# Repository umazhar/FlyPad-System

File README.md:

# FlyPadUI and STROBE

## Overview
FlyPadUI (Sip TRiggered Optogenetic Behavior Enclosure) is a Python-based user interface for tracking fly sips, calculating preference indices, and providing a convenient graphical interface for data analysis. The software connects to the STROBE device to record and analyze feeding behavior in flies.

The original STROBE UI was built in Visual Studio 2012 in C++ on Windows 10 and required installation of Qt 5.11 to compile. The current Python-based version maintains compatibility with the STROBE device while providing improved usability and analysis capabilities.

## Requirements
- Python (latest version)
- Dependencies listed in `requirements.txt`

## Installation

1. Clone this repository:
```bash
git clone https://github.com/umazhar/STROBE.git
cd /SOFTWARE/STROBE_UI
```

2. Create and activate a virtual environment

**For Linux/Mac (Terminal):**
```bash
python -m venv venv
source venv/bin/activate
```

**For Windows (Command Prompt):**
```cmd
python -m venv venv
venv\Scripts\activate.bat
```

**For Windows (PowerShell):**
```powershell
python -m venv venv
.\venv\Scripts\Activate.ps1
```

1. Install required dependencies:
```bash
pip install -r requirements.txt
```

## Usage

Run the main application:
```bash
python main.py
```

All output data will be stored in the `output` folder.

## File Structure
```
/SOFTWARE/STROBE_UI/
├── main.py           # Main application entry point
├── requirements.txt  # Dependencies
├── venv/             # Virtual environment (generated on setup)
└── output/           # Output data directory
```

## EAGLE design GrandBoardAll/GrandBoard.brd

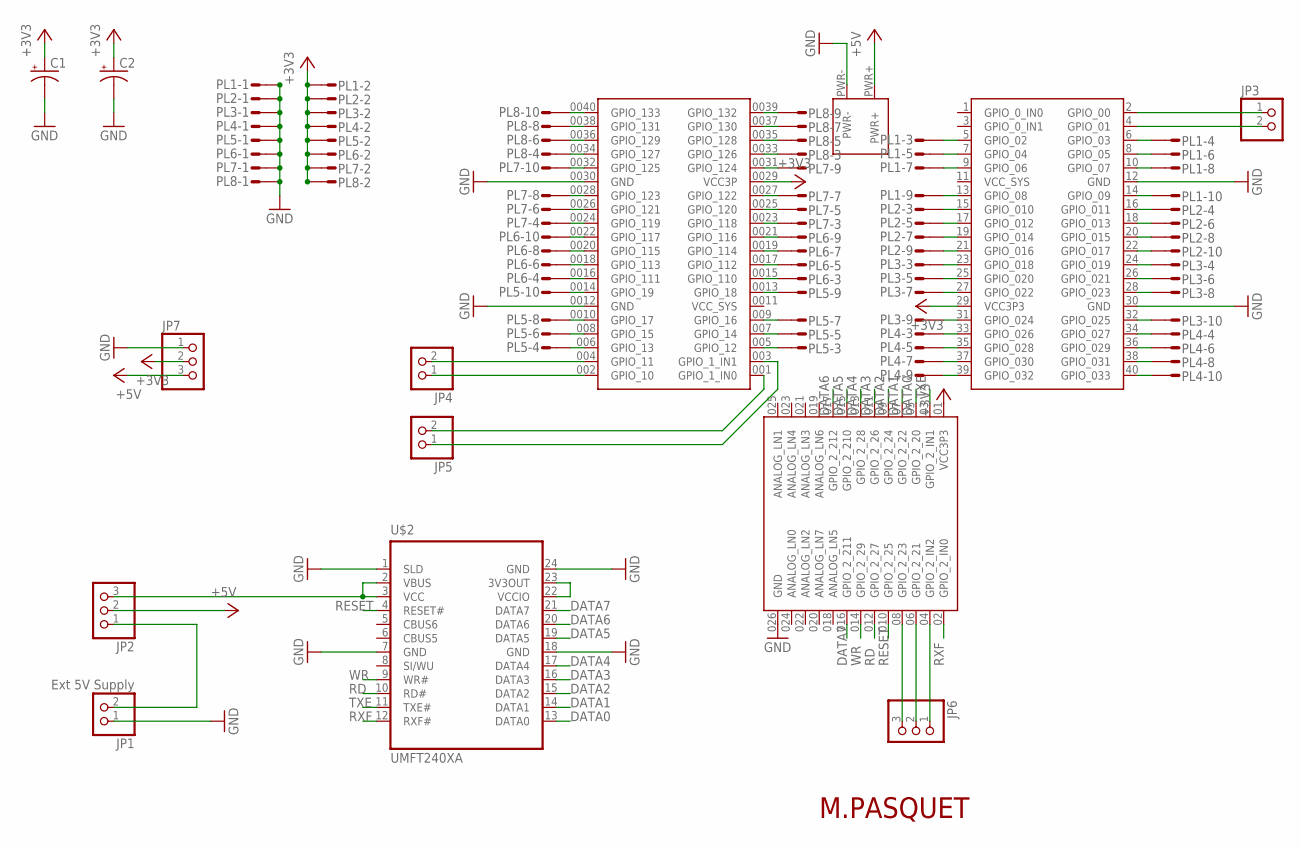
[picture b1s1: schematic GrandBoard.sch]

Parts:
C1, C2: CAP_POLPTH2; CPOL-RADIAL-10UF-25V
JP1: Ext 5V Supply; 1X02
JP2, JP6, JP7: PINHD-1X3; 1X03
JP3, JP4, JP5: PINHD-1X2; 1X02
PL1, PL2, PL3, PL4, PL5, PL6, PL7, PL8: 10HS; 10H
U$1: DE0-NANO
U$2: UMFT240XA

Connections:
+3V3: C1.1 (+), C2.1 (+), JP7.2, PL1.2, PL2.2, PL3.2, PL4.2, PL5.2, PL6.2, PL7.2, PL8.2, U$1.01 (VCC3P3), U$1.0029 (VCC3P), U$1.29 (VCC3P3)
+5V: JP2.2, JP7.3, U$1.PWR+
DATA0: U$1.05 (GPIO_2_20), U$2.13 (DATA0)
DATA1: U$1.07 (GPIO_2_22), U$2.14 (DATA1)
DATA2: U$1.09 (GPIO_2_24), U$2.15 (DATA2)
DATA3: U$1.011 (GPIO_2_26), U$2.16 (DATA3)
DATA4: U$1.013 (GPIO_2_28), U$2.17 (DATA4)
DATA5: U$1.015 (GPIO_2_210), U$2.19 (DATA5)
DATA6: U$1.017 (GPIO_2_212), U$2.20 (DATA6)
DATA7: U$1.016 (GPIO_2_211), U$2.21 (DATA7)
GND: C1.2 (-), C2.2 (-), JP1.1, JP7.1, PL1.1, PL2.1, PL3.1, PL4.1, PL5.1, PL6.1, PL7.1, PL8.1, U$1.12 (GND), U$1.0012 (GND), U$1.026 (GND), U$1.0030 (GND), U$1.30 (GND), U$1.PWR-, U$2.1 (SLD), U$2.7 (GND), U$2.18 (GND), U$2.24 (GND)
unnamed: PL1.3, U$1.5 (GPIO_02)
unnamed: PL1.4, U$1.6 (GPIO_03)
unnamed: PL1.5, U$1.7 (GPIO_04)
unnamed: PL1.6, U$1.8 (GPIO_05)
unnamed: PL1.7, U$1.9 (GPIO_06)
unnamed: PL1.8, U$1.10 (GPIO_07)
unnamed: PL1.9, U$1.13 (GPIO_08)
unnamed: PL1.10, U$1.14 (GPIO_09)
unnamed: PL2.3, U$1.15 (GPIO_010)
unnamed: PL2.4, U$1.16 (GPIO_011)
unnamed: PL2.5, U$1.17 (GPIO_012)
unnamed: PL2.6, U$1.18 (GPIO_013)
unnamed: PL2.7, U$1.19 (GPIO_014)
unnamed: PL2.8, U$1.20 (GPIO_015)
unnamed: PL2.9, U$1.21 (GPIO_016)
unnamed: PL2.10, U$1.22 (GPIO_017)
unnamed: PL3.3, U$1.23 (GPIO_018)
unnamed: PL3.4, U$1.24 (GPIO_019)
unnamed: PL3.5, U$1.25 (GPIO_020)
unnamed: PL3.6, U$1.26 (GPIO_021)
unnamed: PL3.7, U$1.27 (GPIO_022)
unnamed: PL3.8, U$1.28 (GPIO_023)
unnamed: PL3.9, U$1.31 (GPIO_024)
unnamed: PL3.10, U$1.32 (GPIO_025)
unnamed: PL4.3, U$1.33 (GPIO_026)
unnamed: PL4.4, U$1.34 (GPIO_027)
unnamed: PL4.6, U$1.36 (GPIO_029)
unnamed: PL4.5, U$1.35 (GPIO_028)
unnamed: PL4.7, U$1.37 (GPIO_030)
unnamed: PL4.8, U$1.38 (GPIO_031)
unnamed: PL4.9, U$1.39 (GPIO_032)
unnamed: PL4.10, U$1.40 (GPIO_033)
unnamed: PL5.3, U$1.005 (GPIO_12)
unnamed: PL5.4, U$1.006 (GPIO_13)
unnamed: PL5.5, U$1.007 (GPIO_14)
unnamed: PL5.6, U$1.008 (GPIO_15)
unnamed: PL5.7, U$1.009 (GPIO_16)
unnamed: PL5.8, U$1.0010 (GPIO_17)
unnamed: PL5.9, U$1.0013 (GPIO_18)
unnamed: PL5.10, U$1.0014 (GPIO_19)
unnamed: PL6.3, U$1.0015 (GPIO_110)
unnamed: PL6.4, U$1.0016 (GPIO_111)
unnamed: PL6.5, U$1.0017 (GPIO_112)
unnamed: PL6.6, U$1.0018 (GPIO_113)
unnamed: PL6.7, U$1.0019 (GPIO_114)
unnamed: PL6.8, U$1.0020 (GPIO_115)
unnamed: PL6.9, U$1.0021 (GPIO_116)
unnamed: PL6.10, U$1.0022 (GPIO_117)
unnamed: PL7.3, U$1.0023 (GPIO_118)
unnamed: PL7.4, U$1.0024 (GPIO_119)
unnamed: PL7.5, U$1.0025 (GPIO_120)
unnamed: PL7.6, U$1.0026 (GPIO_121)
unnamed: PL7.7, U$1.0027 (GPIO_122)
unnamed: PL7.8, U$1.0028 (GPIO_123)
unnamed: PL7.9, U$1.0031 (GPIO_124)
unnamed: PL7.10, U$1.0032 (GPIO_125)
unnamed: PL8.3, U$1.0033 (GPIO_126)
unnamed: PL8.4, U$1.0034 (GPIO_127)
unnamed: PL8.5, U$1.0035 (GPIO_128)
unnamed: PL8.6, U$1.0036 (GPIO_129)
unnamed: PL8.7, U$1.0037 (GPIO_130)
unnamed: PL8.8, U$1.0038 (GPIO_131)
unnamed: PL8.9, U$1.0039 (GPIO_132)
unnamed: PL8.10, U$1.0040 (GPIO_133)
unnamed: U$2.22 (VCCIO), U$2.23 (3V3OUT)
unnamed: JP2.3, U$2.2 (VBUS), U$2.3 (VCC)
unnamed: JP1.2, JP2.1
unnamed: JP3.1, U$1.2 (GPIO_00)
unnamed: JP3.2, U$1.4 (GPIO_01)
unnamed: JP4.1, U$1.002 (GPIO_10)
unnamed: JP4.2, U$1.004 (GPIO_11)
unnamed: JP5.1, U$1.003 (GPIO_1_IN1)
unnamed: JP5.2, U$1.001 (GPIO_1_IN0)
unnamed: JP6.1, U$1.04 (GPIO_2_IN2)
unnamed: JP6.2, U$1.06 (GPIO_2_21)
unnamed: JP6.3, U$1.08 (GPIO_2_23)
RD: U$1.012 (GPIO_2_27), U$2.10 (RD#)
RESET: U$1.010 (GPIO_2_25), U$2.4 (RESET#)
RXF: U$1.02 (GPIO_2_IN0), U$2.12 (RXF#)
TXE: U$1.03 (GPIO_2_IN1), U$2.11 (TXE#)
WR: U$1.014 (GPIO_2_29), U$2.9 (WR#)

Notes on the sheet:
M.PASQUET

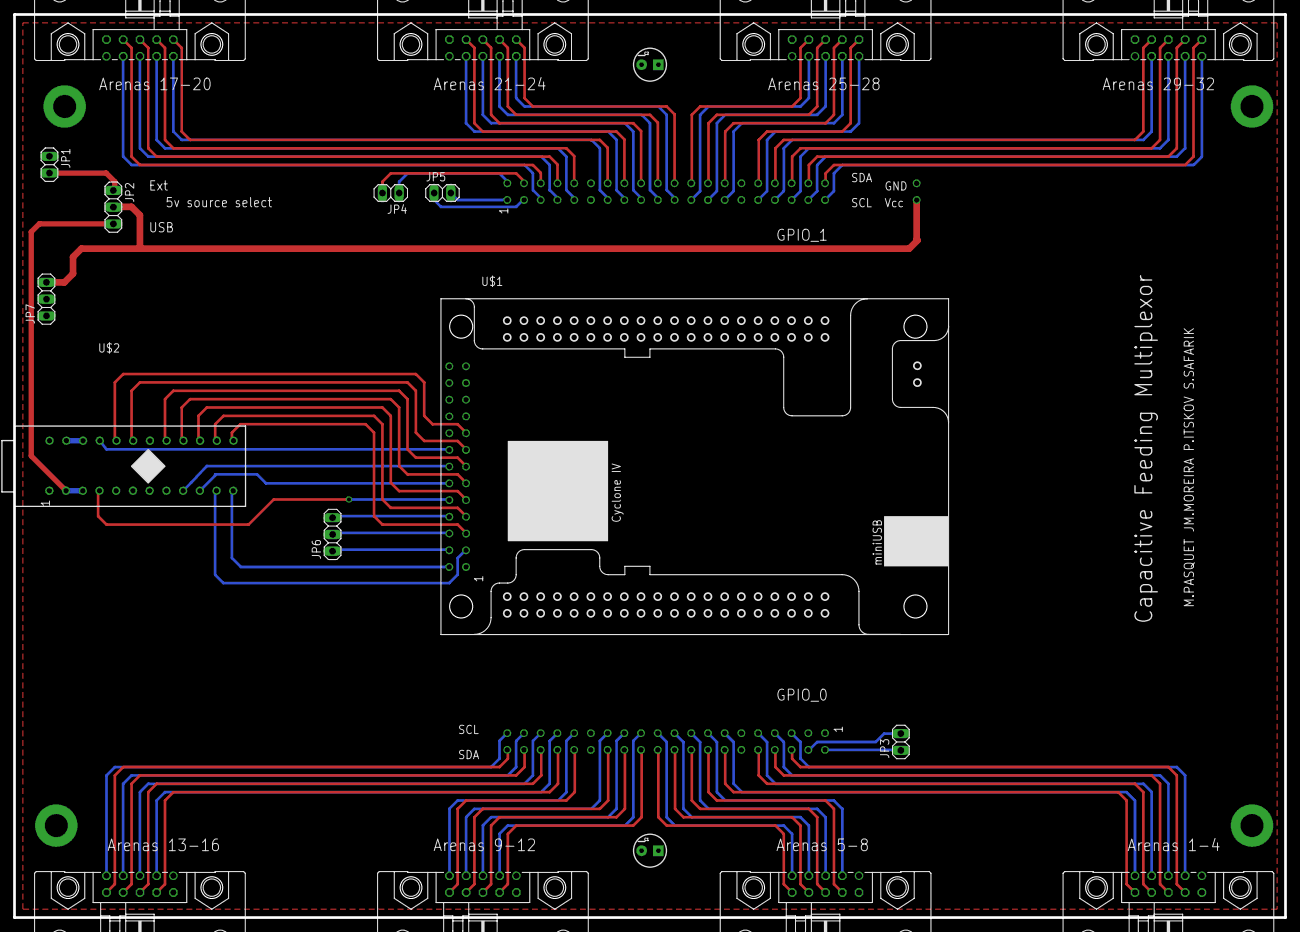
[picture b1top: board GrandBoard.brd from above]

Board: 2 copper layers, 193.0 x 137.2 mm, 19 parts (0 on the bottom side), 92 nets.

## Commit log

2018-05-31 Initial commit of post-processing scripts, executables, and FPGA source files
2018-08-02 Add UI source
2018-08-02 Initial commit of README
2018-08-20 All files uploaded
2018-08-23 Removing blueprint files
2018-08-27 Add STROBE changeset
2018-08-27 Remove FPGA source
2018-08-31 Add GNU GPL 2.0 license
2022-07-12 fixed wallpaper colour
2024-10-17 Fixed fodler structure
2024-11-22 updated main and post strobe lib
2025-02-10 added new code
2025-02-10 Added feature to save logs into a folder
2025-02-10 Added sip features and preference index feature
2025-02-10 Updated to new UI, improved debug to work with 2 sensors
2025-03-18 commiting old code for storage
2025-03-18 Added code from other repo, changed directory structure, working UI
2025-03-20 Fixed sensor to take in differences rather than threshold, added change arena #s, restart test button
2025-03-20 commented out debug for now
2025-03-25 changed names for left and right sensor to make it more clear
2025-04-03 testing code doesnt work
2025-04-08 update raedme with diff OS activate
2025-04-08 fixed readme
2025-04-09 added sensor highlighting and auto calibration
2025-04-09 fixed overhang bug
2025-04-09 fixed extra file bug
2025-04-09 fixed preference index
2025-04-09 forgot to fix prefernce in data logger oops
2025-04-10 changed left/right to blue/red
2025-04-12 added firmware ui from other repo
2025-04-12 changed name from STROBE to FlyPad
2025-04-24 Added windows support, use FTD2XX library if windows detected
2025-04-24 changed latency to 2ms from 16 ms
2025-04-24 removed sip data
2025-04-25 added ftd2xx to requirements
2025-04-25 fixed port name bug

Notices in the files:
parts and their libraries:
SparkFun-Passives: Licensing: CC v3.0 Share-Alike You are welcome to use this library for commercial purposes.
